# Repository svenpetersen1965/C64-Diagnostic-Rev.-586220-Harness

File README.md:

# C64-Diagnostic-Rev.-586220-Harness
The Diagnostic Rev. 586220 is a widely accepted test tool for the Commodore C64. It tests the RAM, ROMs and 
the peripheral chips (VIC, SID, CIA). To test all interfaces, a feedback is required. This is provided by this harness.

Find more information about the cable making involved <a href="http://tech.guitarsite.de/cable_making.html">on my website</a>

# Rev. 0

This repository contains all eagle files, gerber files, BOM, descriptions and cable drawings. The main documentation is contained in the User Port section.

Depending on where the parts and pcbs are purchased, the price for the complete harness is less than 20€ (2019).

Now, a 3D printed case for the user port and the cassette donge is designed and the stl files etc. are available here. 

# Rev. 1
Revision 1 is released now. It fixes the "False OK" of the Control Port test, while the keyboard dongle is inserted. This is a phenomenon, that applies to all sorts of harnesses for Diagnostic Rev. 586220. Please refer to <a src="http://tech.guitarsite.de/c64_diag_harness.html">my website</a>

# Extended Keyboard Dongle (do not build, unless you are sure, what it is required for)
A fix for existing harnesses is the <b>extended</b> Keyboard Dongle. It can be combined with Rev. 0 of this harness and all other Harnesses. It only requires a connection to the Cassette Port Dongle. It is not required with Rev. 1 of the harness or later. 

# Keyboard dongle with 90° header
Some people want to test the C64 mainboard while being mounted. The keyboard cable connector is conflicting here. Some leave out the strain relief. This is not a great solution. A 90° boc pin header can be used insted of the vertical one. This swapps the pins, due to a different orientation. Since the symmetrical pinning of the header and the non-directional properties of the analog switches, this does not matter and is working fine. I only build this kind of KB dongle now.

# The SMD Version
This version has no functional updates compared to Rev. 2 of the UP PCB and Rev. 1 of the Cassette SMD. Some prefer building SMD assemblies (me included). It is now fully tested.

# Recommended Screws
* For the case, I have used 2.9mm x 9.5mm (self taping) screws for sheet metal (C 2,9x9,5H, DIN 7981).  
* For mounting the optional slide switch: DIN 7985, M2x6
* For mounting the optional voltmeter: 2.2mm x 4.5mm (self taping) screws for sheet metal (C 2,2x4,5H, DIN 7981). 

# C128 diagnostics
They keyboard PCB for the C128 is released now and included in this repository. 

A cartridge with the Diagnostic Rev. 785260 software is required. I recommend using the <a href="https://github.com/bwack/Versa64Cart">Versa64cart</a> for this purpose. Other 8k generic cartridges might also be working. /EXROM and /GAME have to be HIGH/open.

The <b>C128D and C128D-CR</b> require a longer cable (1m) between the user port PCB and the Cassette port dongle. Both work with the <b>C128D Diagnostic Rev. 785260</b>.  The keyboard ribbon cable should be 90cm for the C128D.

The cassette port ribbon cable requires to be 25cm long for the C128 and 70cm long for the C128D/DCR.

The <b>C128D-CR</b> does not provide +5V at the keyboard D-Sub jack. The keyboard dongle <b>does not work</b> here. A solution needs to be developed.  

I have noticed, that not all female D-Sub connectors provide a proper contact with the pin header on the C128 mainboard. Please keep this in mind. The recommended type is Amphenol/FCI DB25S064TLF (Digikey 609-1519-ND, more sources in the BOM v1.1 or later). 

You might want to check out the 3D printed dongle case from <a href="https://www.thingiverse.com/thing:4602956">retrorewind.ca</a>.

# SX-64 Diagnostics
Diagnosing an SX/64 requires disconnecting the internal disk drive. A cassette port dongle cannot be used, so the analog switches for testing the control ports need to be switched manually. This is an option with teh User Port PCB Rev. 2.

Also the Keyboard can be tested with the C128 KB dongle and a gender changer.

The Diagnostic Rev. 586220++ is capable of detecting the SX-64 Kernal and then skip testing the cassette port.

# Other
you might want to check Jeff Birt's <a href="https://github.com/Jeff-Birt/COREi64_Dual_Diag_Cart_Case/tree/master">case</a> for the harness, too.

Find additional info about the harness on my <a href="http://tech.guitarsite.de/c64_diag_harness.html">website</a>.

Jeff Birt provided the information of the cable lengths for C128 diagnostics. This is part of the documentation now. 

# User Port PCB Rev. 2
The user Port PCB Rev. 2 fits into the User Port Case Rev. 1. It adds an option for the SX-64: Since the SX-64 has no
Cassette Port, the Feedbacks for the CVontrol Port are not switched automatically by the software. Rev. 2 allows to
switch on the feedbacks manually. A User Port Case for thei option has been made. It incorporates a cut out for a slide
switch (standard 19mm hole pitch). This switch can be connected top JP1. For this option the cutpad has to be cut open. 

# User Port PCB Rev. 3

The User Port Rev. 3 Dongle (THT and SMD versions in this repository) is providing two LED for voltage intocations (+5V and 9VAC). Further, there are pin headers for measuring those voltages at the user port. The +5V pin header allows connecting a 4 digit "precision" panel meter. I have some trust issues with those panel meters, but they are a nice light show.  

Nov. 2024: There is a new version of the case (the STLs are ending on "_noVM_SX.stl"). This version allows to measure the voltages at the pin headers with your multimeter and configure the SX64 or C64 option via jumper. That jumper should be the type with a "handle". 

<b>The solder bridge JP1 near the pin header J6 (which has to be placed) needs to be open!</b>

Therefore, it has to be cut along the gap with a scalpel or exacto knife. It is best to check the success with an ohmmeter/multimeter.

The cable for measuring the voltage (+5VDC and 9VAC) at the pin pin headers consists of two AWG24 wires, preferable in different colors, on one end is a two way Dupont connector, on the other end 4mm lab connectors. Holding them together with cable ties is maybe not such a bad idea.

To prevent short circuit, you should plug the lab connectors in the multimeter first, there are some security multimeter connectors, too. 

# Analog Switch IC (User Port Dongle)
Originally, the analog switches are <b>4066</b>. The 74HC4066 was also tested and works perfectly.

# BOM Value
The BOM values are calculated in May 2020. The calculation is based on the item prices from reichelt.de. They might differ from distributor to distributor. The edge connector prices are based on ebay shoppings. The calculated prices do not include any shipping fees. 

* User Port PCB plus cables and IEC dongle: 13.38€
* Cassette Port Dongle: 4.99€
* Keyboard Dongle: 1.85€
* C128 Keyboard Dongle: 3.23€

The 3D printed cases and the labels are not included in the price calculation.

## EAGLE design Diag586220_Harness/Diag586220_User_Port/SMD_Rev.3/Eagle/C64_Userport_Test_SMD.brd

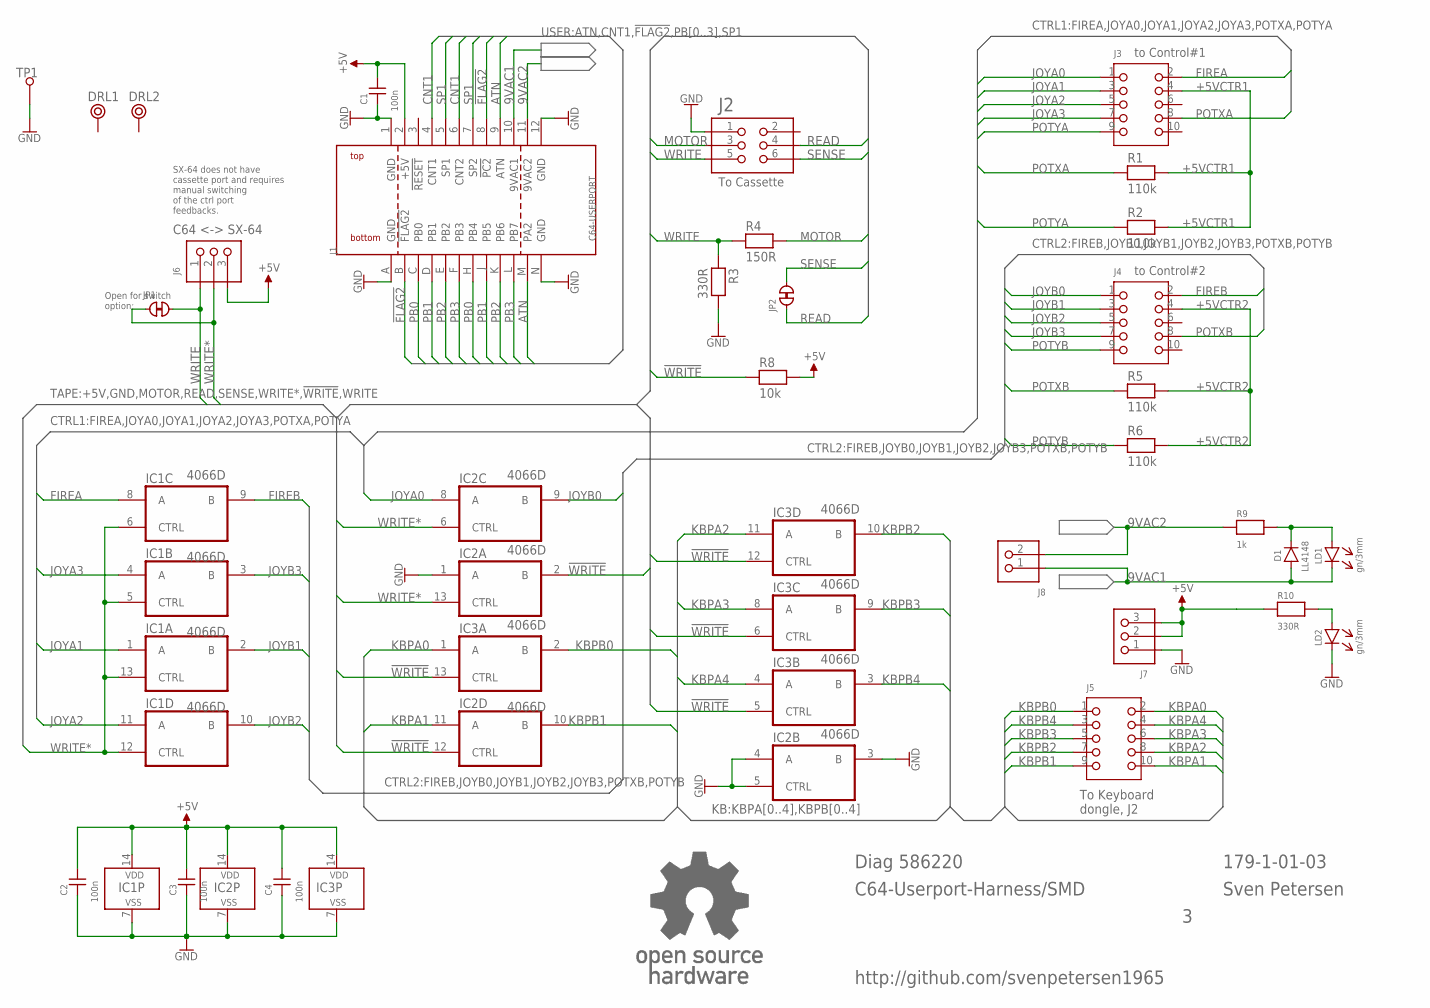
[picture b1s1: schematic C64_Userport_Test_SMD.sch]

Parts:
C1, C2, C3, C4: 100n; 0805
D1: LL4148; SOD80C
DRL1, DRL2: BOHR3,2
IC1, IC2, IC3: 4066D; SO14
J1: C64-USERPORT; USERPORT
J2: 2X03WV
J3, J4, J5: 2X05WV
J6, J7: PINHD-1X3; 1X03
J8: PINHD-1X2; 1X02
JP1, JP2: CLOSED; CP_CL
LD1, LD2: gn/3mm; 3MM
R1, R2, R5, R6: 110k; 0805
R3, R10: 330R; 0805
R4: 150R; 0805
R8: 10k; 0805
R9: 1k; 0805
TP1: L1,2_R; 1,2MM_R
U$20: OPEN_SOURCE_HW; OPENHW

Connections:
9VAC1: D1.A, J1.10 (9VAC1), J8.1, LD1.C (K)
9VAC2: J1.11 (9VAC2), J8.2, R9.1
!FLAG2: J1.8 (!PC2), J1.B (!FLAG2)
!WRITE: IC2.2 (B), IC2.12 (CTRL), IC3.5 (CTRL), IC3.6 (CTRL), IC3.12 (CTRL), IC3.13 (CTRL), R8.1
+5V: C1.2, C2.2, C3.2, C4.2, IC1.14 (VDD), IC2.14 (VDD), IC3.14 (VDD), J1.2 (+5V), J6.3, J7.2, J7.3, R8.2, R10.1
+5VCTR1: J3.4, R1.2, R2.2
+5VCTR2: J4.4, R5.2, R6.2
ATN: J1.9 (ATN), J1.M (PA2)
CNT1: J1.4 (CNT1), J1.6 (CNT2)
FIREA: IC1.8 (A), J3.2
FIREB: IC1.9 (B), J4.2
GND: C1.1, C2.1, C3.1, C4.1, IC1.7 (VSS), IC2.1 (A), IC2.3 (B), IC2.4 (A), IC2.5 (CTRL), IC2.7 (VSS), IC3.7 (VSS), J1.1 (GND), J1.12 (GND), J1.A (GND), J1.N (GND), J2.1, J7.1, LD2.C (K), R3.2, TP1.1
JOYA0: IC2.8 (A), J3.1
JOYA1: IC1.1 (A), J3.3
JOYA2: IC1.11 (A), J3.5
JOYA3: IC1.4 (A), J3.7
JOYB0: IC2.9 (B), J4.1
JOYB1: IC1.2 (B), J4.3
JOYB2: IC1.10 (B), J4.5
JOYB3: IC1.3 (B), J4.7
KBPA0: IC3.1 (A), J5.2
KBPA1: IC2.11 (A), J5.10
KBPA2: IC3.11 (A), J5.8
KBPA3: IC3.8 (A), J5.6
KBPA4: IC3.4 (A), J5.4
KBPB0: IC3.2 (B), J5.1
KBPB1: IC2.10 (B), J5.9
KBPB2: IC3.10 (B), J5.7
KBPB3: IC3.9 (B), J5.5
KBPB4: IC3.3 (B), J5.3
MOTOR: J2.3, R4.2
unnamed: D1.K, LD1.A, R9.2
unnamed: LD2.A, R10.2
PB0: J1.C (PB0), J1.H (PB4)
PB1: J1.D (PB1), J1.J (PB5)
PB2: J1.E (PB2), J1.K (PB6)
PB3: J1.F (PB3), J1.L (PB7)
POTXA: J3.8, R1.1
POTXB: J4.8, R5.1
POTYA: J3.9, R2.1
POTYB: J4.9, R6.1
READ: J2.4, JP2.1
SENSE: J2.6, JP2.2
SP1: J1.5 (SP1), J1.7 (SP2)
WRITE: J2.5, J6.1, JP1.2, R3.1, R4.1
WRITE*: IC1.5 (CTRL), IC1.6 (CTRL), IC1.12 (CTRL), IC1.13 (CTRL), IC2.6 (CTRL), IC2.13 (CTRL), J6.2, JP1.1

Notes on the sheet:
Diag 586220
C64-Userport-Harness/SMD
Sven Petersen
To Cassette
to Control#1
to Control#2
179-1-01-03
To Keyboard dongle, J2
C64 <-> SX-64
Open for switch option:
SX-64 does not have cassette port and requires manual switching of the ctrl port feedbacks.
http://github.com/svenpetersen1965

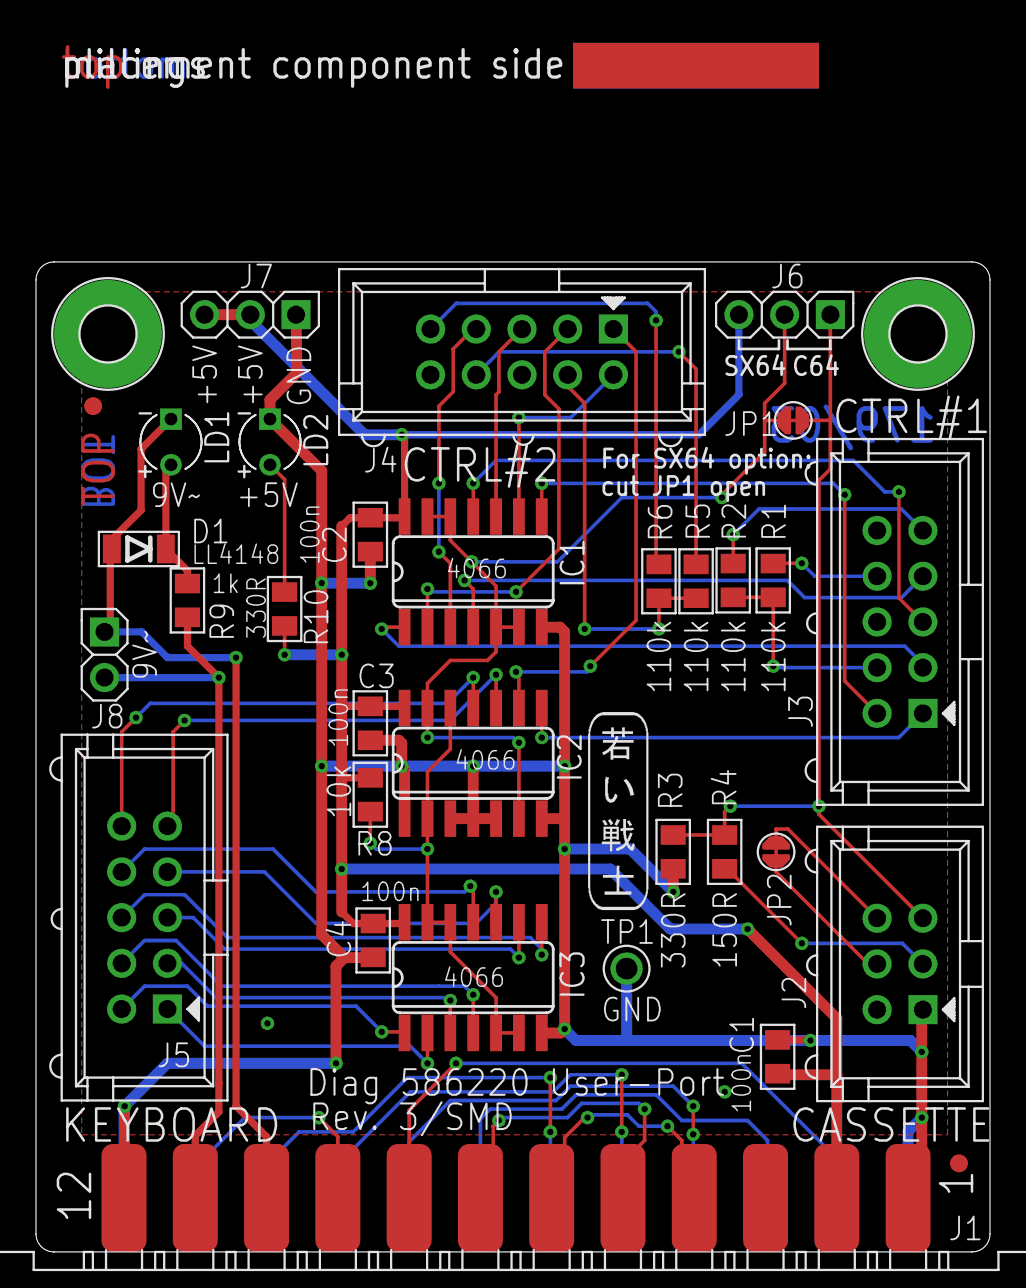
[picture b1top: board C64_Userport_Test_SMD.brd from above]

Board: 2 copper layers, 53.0 x 67.6 mm, 38 parts (1 on the bottom side), 46 nets.

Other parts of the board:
U$15: SVEN_TAG
U$17: 2LAYER
U$18: PCB-TITLE/
U$21, U$22: SMD_REF_R1MM

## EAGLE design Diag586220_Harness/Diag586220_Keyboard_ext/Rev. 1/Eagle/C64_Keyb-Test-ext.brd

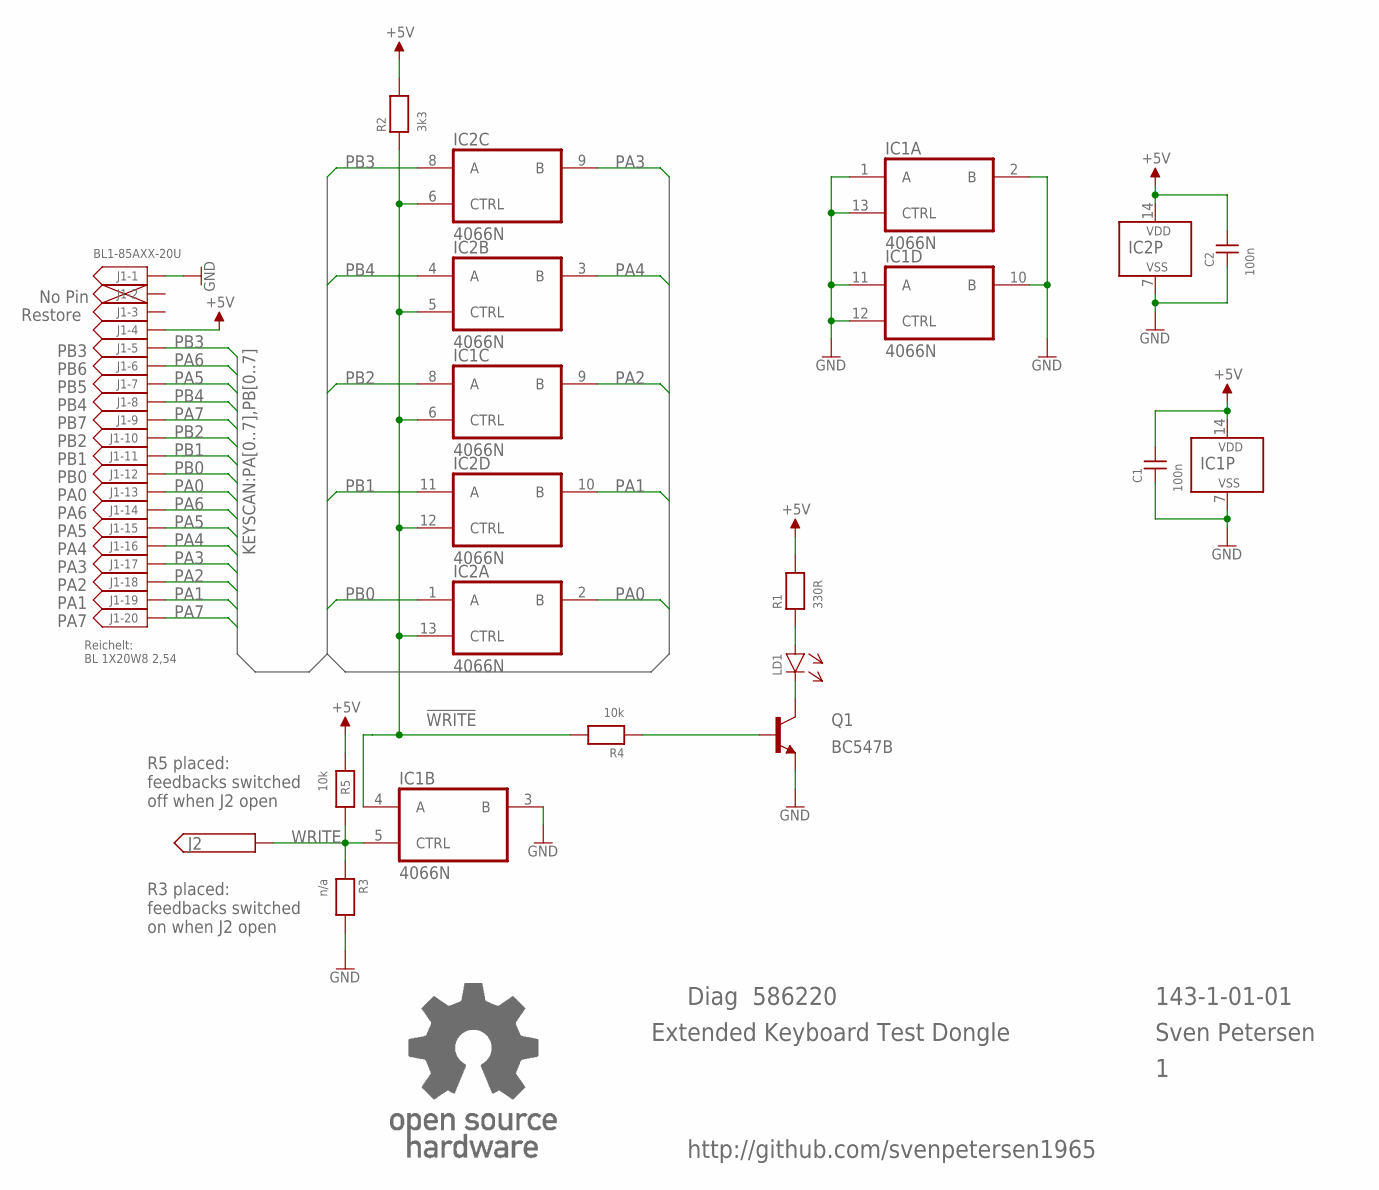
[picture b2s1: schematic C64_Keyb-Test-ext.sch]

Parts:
C1, C2: 100n; C-2,5
IC1, IC2: 4066N; DIL14
J1: BL1-85AXX-20U
J2: PINHD-1X1; 1X01
LD1: 3MM
Q1: BC547B; TO92
R1: 330R; R-10
R2: 3k3; R-10
R3: n/a; R-10
R4, R5: 10k; R-10
U$19: OPEN_SOURCE_HW; OPENHW

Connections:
!WRITE: IC1.4 (A), IC1.6 (CTRL), IC2.5 (CTRL), IC2.6 (CTRL), IC2.12 (CTRL), IC2.13 (CTRL), R2.1, R4.2
+5V: C1.2, C2.2, IC1.14 (VDD), IC2.14 (VDD), J1.4, R1.2, R2.2, R5.1
GND: C1.1, C2.1, IC1.1 (A), IC1.2 (B), IC1.3 (B), IC1.7 (VSS), IC1.10 (B), IC1.11 (A), IC1.12 (CTRL), IC1.13 (CTRL), IC2.7 (VSS), J1.1, Q1.1 (E), R3.2
unnamed: LD1.A, R1.1
unnamed: LD1.C (K), Q1.3 (C)
unnamed: Q1.2 (B), R4.1
PA0: IC2.2 (B), J1.13
PA1: IC2.10 (B), J1.19
PA2: IC1.9 (B), J1.18
PA3: IC2.9 (B), J1.17
PA4: IC2.3 (B), J1.16
PA5: J1.7, J1.15
PA6: J1.6, J1.14
PA7: J1.9, J1.20
PB0: IC2.1 (A), J1.12
PB1: IC2.11 (A), J1.11
PB2: IC1.8 (A), J1.10
PB3: IC2.8 (A), J1.5
PB4: IC2.4 (A), J1.8
WRITE: IC1.5 (CTRL), J2.1, R3.1, R5.2

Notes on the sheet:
PB3
PB6
PB5
PB4
PB7
PB2
PB1
PB0
PA0
PA6
PA5
PA4
PA3
PA2
PA1
PA7
No Pin
Restore
Diag 586220
Extended Keyboard Test Dongle
143-1-01-01
Sven Petersen
Reichelt: BL 1X20W8 2,54
R5 placed: feedbacks switched off when J2 open
R3 placed: feedbacks switched on when J2 open
http://github.com/svenpetersen1965

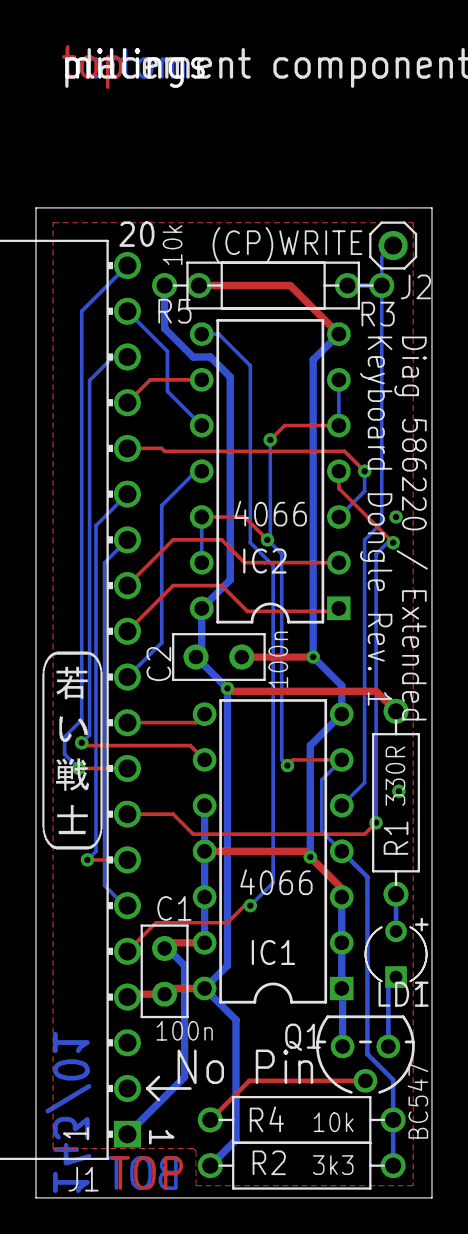
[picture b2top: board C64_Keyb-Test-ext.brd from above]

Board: 2 copper layers, 22.0 x 64.6 mm, 17 parts (1 on the bottom side), 20 nets.

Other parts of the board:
U$6: 2LAYER
U$7: PCB-TITLE/
U$17: SVEN_TAG

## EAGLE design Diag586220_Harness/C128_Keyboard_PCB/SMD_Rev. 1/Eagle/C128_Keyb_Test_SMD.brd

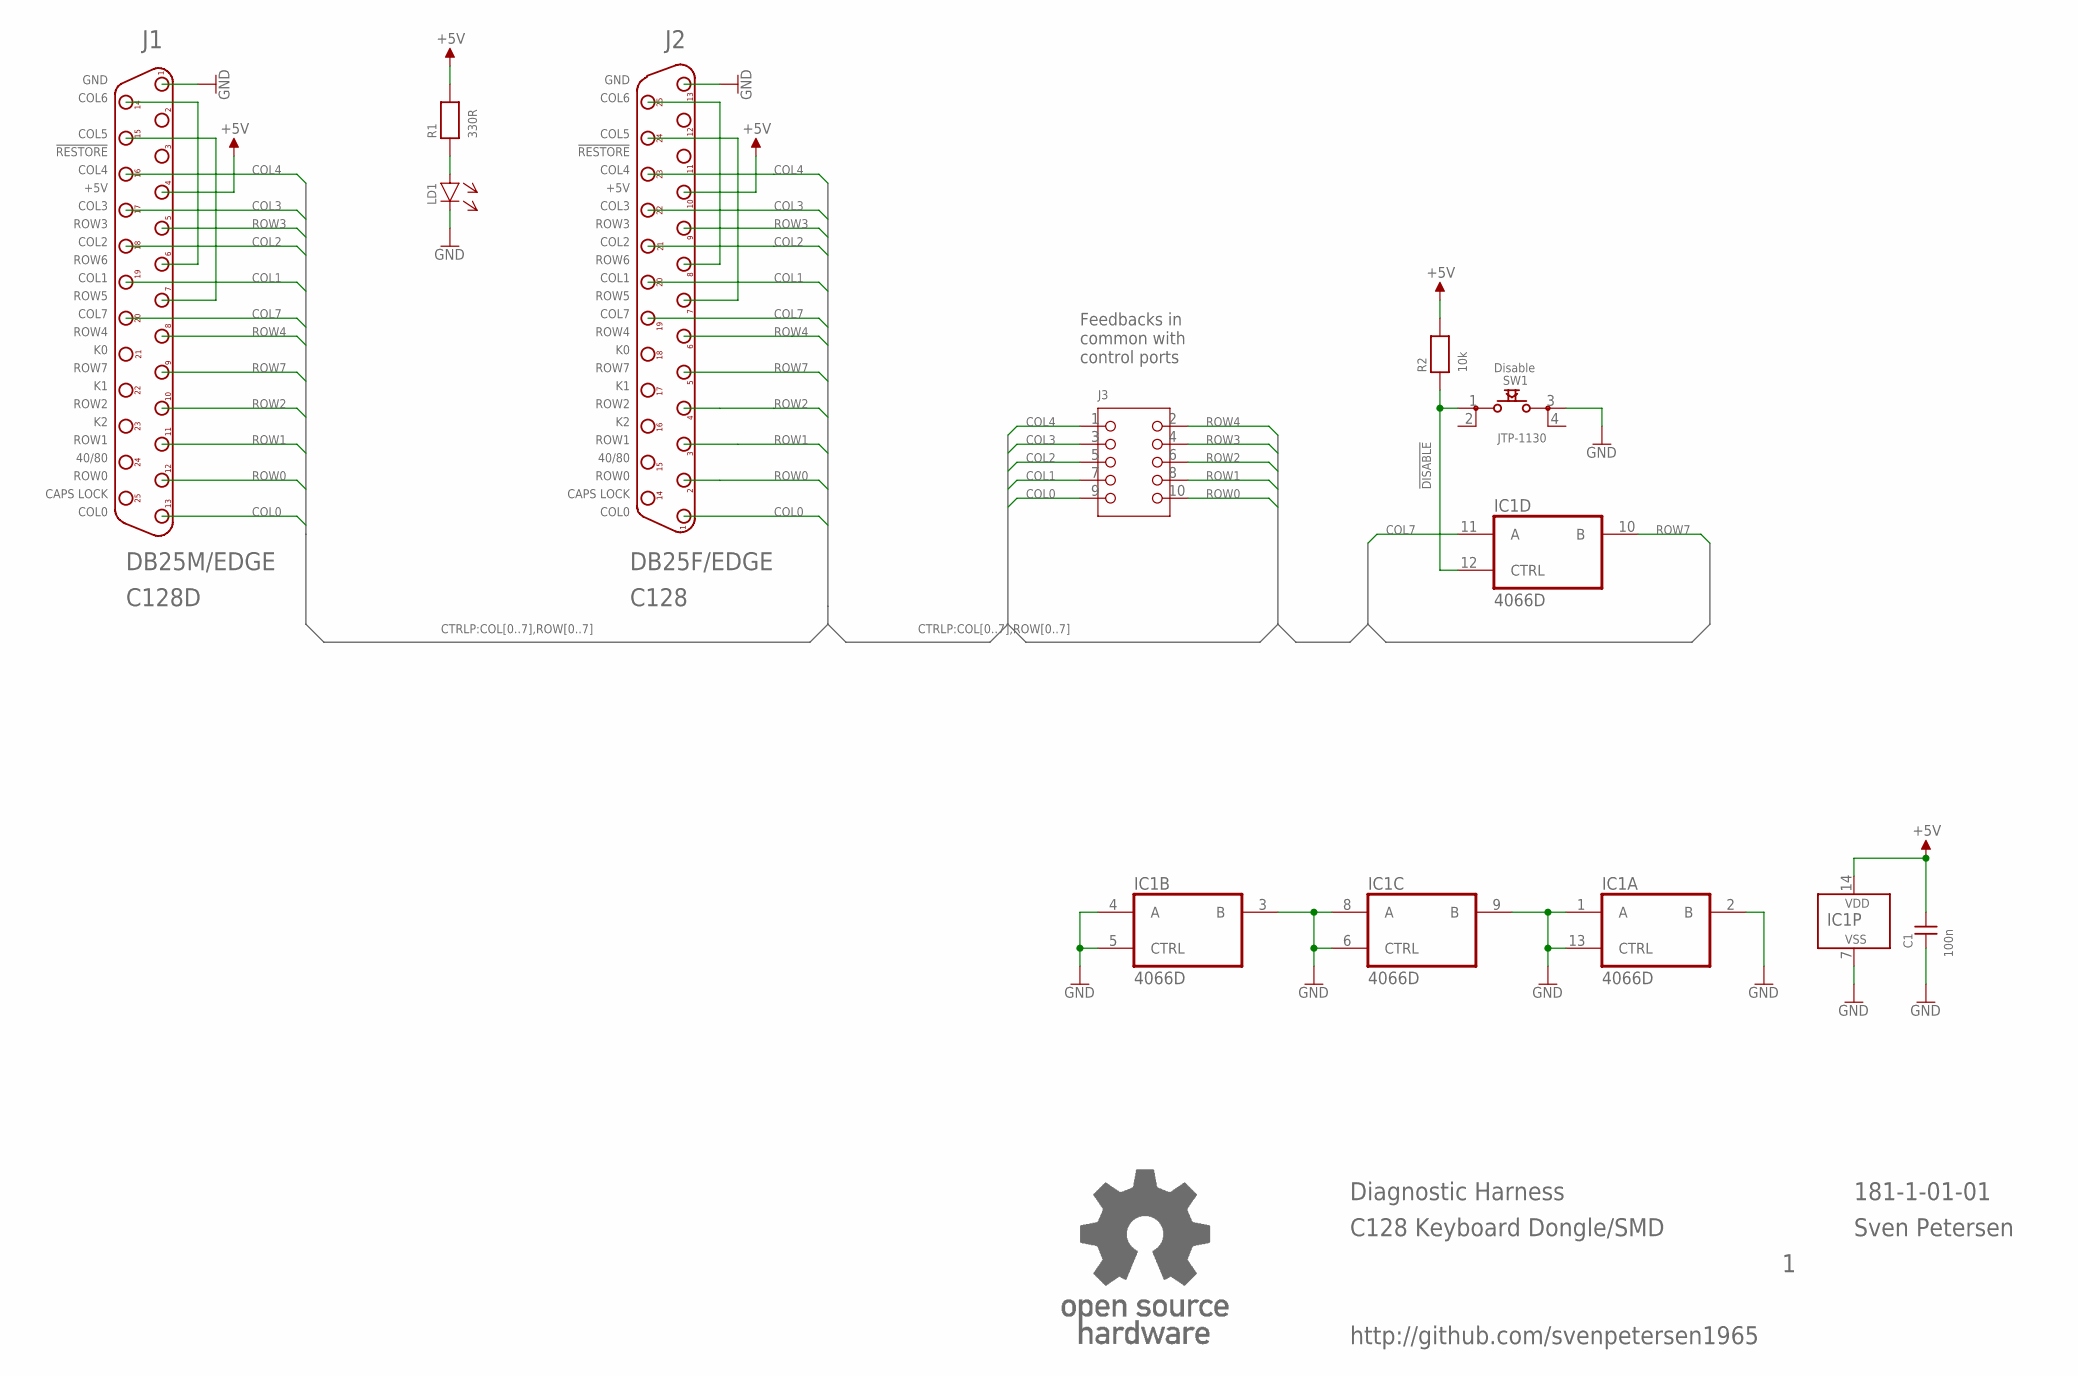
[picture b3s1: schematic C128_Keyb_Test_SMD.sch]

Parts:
C1: 100n; 0805
IC1: 4066D; SO14
J1: DB25M/EDGE; DB25M-EDGE
J2: DB25F/EDGE; DB25F-EDGE
J3: 2X05WV
LD1: 3MM
R1: 330R; 0805
R2: 10k; 0805
SW1: JTP-1130
U$20: OPEN_SOURCE_HW; OPENHW

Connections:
!DISABLE: IC1.12 (CTRL), R2.1, SW1.1
+5V: C1.2, IC1.14 (VDD), J1.4, J2.10, R1.2, R2.2
COL0: J1.13, J2.1, J3.9
COL1: J1.19, J2.20, J3.7
COL2: J1.18, J2.21, J3.5
COL3: J1.17, J2.22, J3.3
COL4: J1.16, J2.23, J3.1
COL7: IC1.11 (A), J1.20, J2.19
GND: C1.1, IC1.1 (A), IC1.2 (B), IC1.3 (B), IC1.4 (A), IC1.5 (CTRL), IC1.6 (CTRL), IC1.7 (VSS), IC1.8 (A), IC1.9 (B), IC1.13 (CTRL), J1.1, J2.13, LD1.C (K), SW1.3
unnamed: J1.6, J1.14
unnamed: J1.7, J1.15
unnamed: LD1.A, R1.1
unnamed: J2.7, J2.24
unnamed: J2.8, J2.25
ROW0: J1.12, J2.2, J3.10
ROW1: J1.11, J2.3, J3.8
ROW2: J1.10, J2.4, J3.6
ROW3: J1.5, J2.9, J3.4
ROW4: J1.8, J2.6, J3.2
ROW7: IC1.10 (B), J1.9, J2.5

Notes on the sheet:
Diagnostic Harness
C128 Keyboard Dongle/SMD
181-1-01-01
Sven Petersen
C128D
C128
ROW0
ROW1
ROW2
ROW3
ROW4
ROW5
ROW6
ROW7
COL0
COL1
COL2
COL3
COL4
COL5
COL6
COL7
!RESTORE
40/80
CAPS LOCK
GND
+5V
Feedbacks in common with control ports
Disable
http://github.com/svenpetersen1965

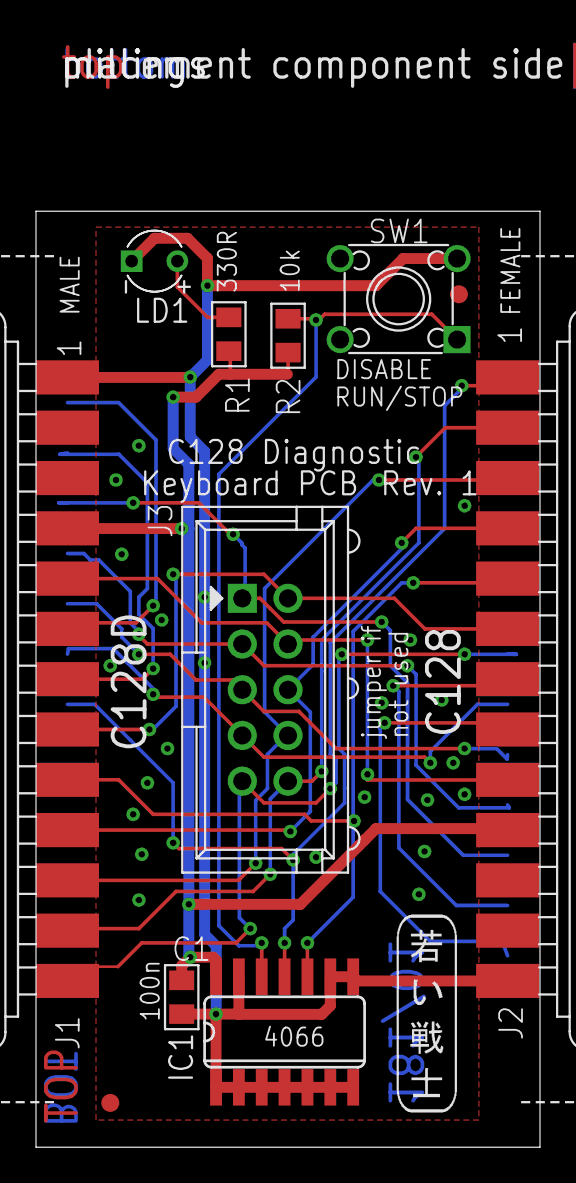
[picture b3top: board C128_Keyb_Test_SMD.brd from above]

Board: 2 copper layers, 28.0 x 61.7 mm, 15 parts (1 on the bottom side), 20 nets.

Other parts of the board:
U$8: 2LAYER
U$9: PCB-TITLE/
U$10: SVEN_TAG
U$21, U$22: SMD_REF_R1MM

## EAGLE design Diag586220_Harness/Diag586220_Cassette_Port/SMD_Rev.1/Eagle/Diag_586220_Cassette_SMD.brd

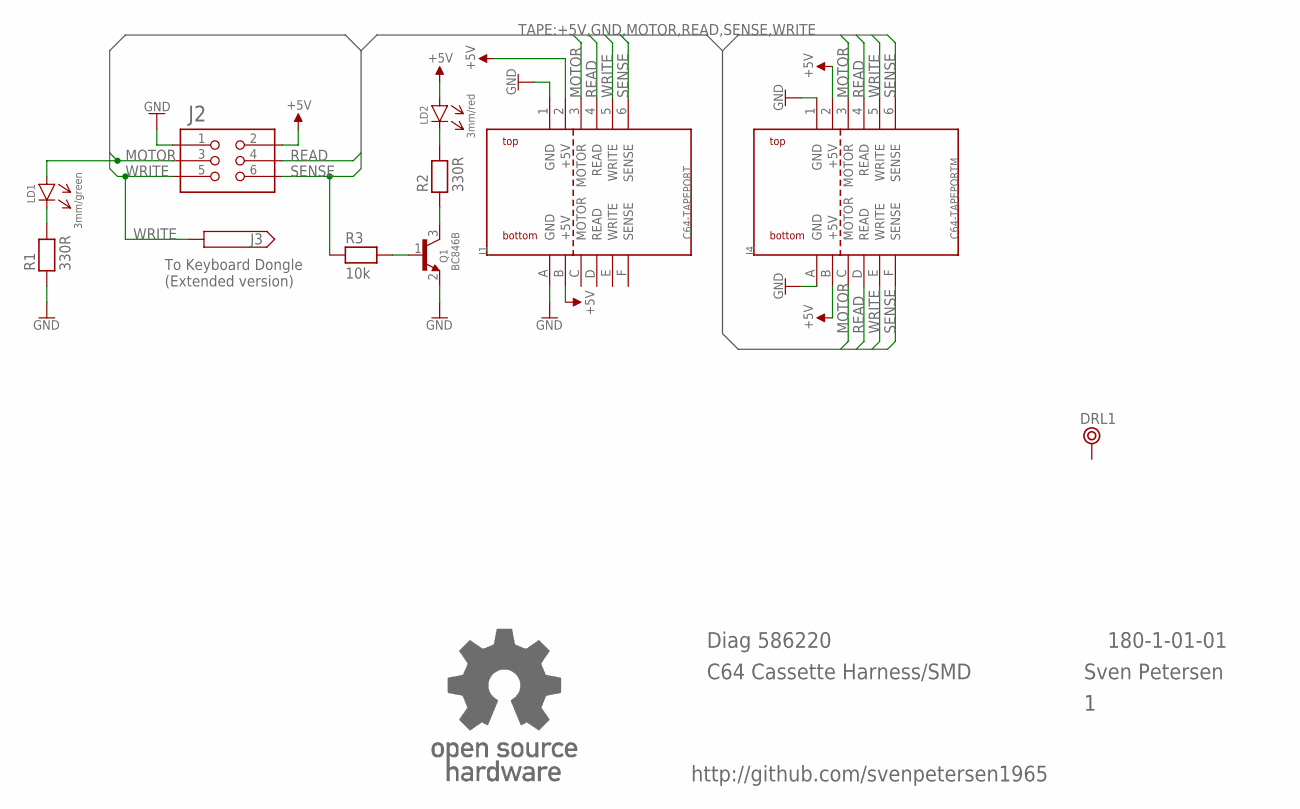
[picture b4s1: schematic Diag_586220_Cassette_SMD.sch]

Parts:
DRL1: BOHR3,5
J1: C64-TAPEPORT; TAPEPORT
J2: 2X03WV
J3: PINHD-1X1; 1X01
J4: C64-TAPEPORTM; TAPEPORT_M
LD1: 3mm/green; 3MM
LD2: 3mm/red; 3MM
Q1: BC846B; SOT23
R1, R2: 330R; 0805
R3: 10k; 0805
U$18: OPEN_SOURCE_HW; OPENHW

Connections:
+5V: J1.2 (+5V), J1.B (+5V), J2.2, J4.2 (+5V), J4.B (+5V), LD2.A
GND: J1.1 (GND), J1.A (GND), J2.1, J4.1 (GND), J4.A (GND), Q1.2 (E), R1.1
MOTOR: J1.3 (MOTOR), J2.3, J4.3 (MOTOR), J4.C (MOTOR), LD1.A
unnamed: LD1.C (K), R1.2
unnamed: Q1.1 (B), R3.2
unnamed: Q1.3 (C), R2.1
unnamed: LD2.C (K), R2.2
READ: J1.4 (READ), J2.4, J4.4 (READ), J4.D (READ)
SENSE: J1.6 (SENSE), J2.6, J4.6 (SENSE), J4.F (SENSE), R3.1
WRITE: J1.5 (WRITE), J2.5, J3.1, J4.5 (WRITE), J4.E (WRITE)

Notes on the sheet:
Diag 586220
C64 Cassette Harness/SMD
Sven Petersen
180-1-01-01
To Keyboard Dongle (Extended version)
http://github.com/svenpetersen1965

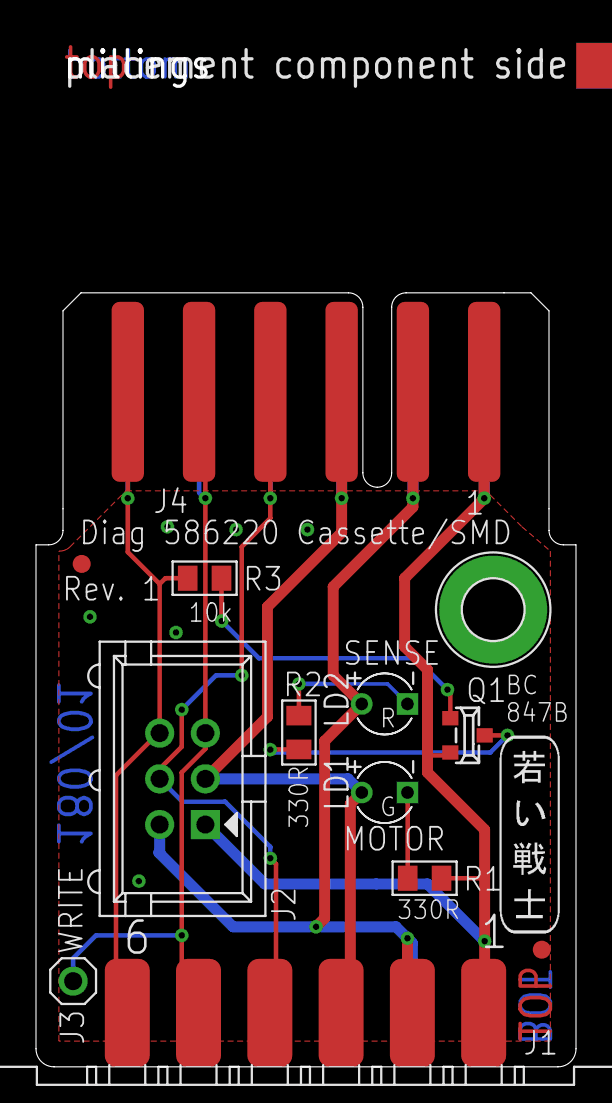
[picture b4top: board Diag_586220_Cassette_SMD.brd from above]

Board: 2 copper layers, 30.0 x 57.3 mm, 17 parts (1 on the bottom side), 10 nets.

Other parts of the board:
U$5: PCB-TITLE/
U$6: 2LAYER
U$11: SVEN_TAG
U$19, U$20: SMD_REF_R1MM

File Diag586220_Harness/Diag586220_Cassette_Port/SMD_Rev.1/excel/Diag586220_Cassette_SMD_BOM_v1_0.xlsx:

Diagnostic Rev. 586220 Harness - Cassette Port SMD Rev. 1
Bill of Material Rev. 1.0
Pos. | Qty | Value | Footprint | Ref.-No. | Comment
1 | 1 | 180-2-01-01 | 2 Layer | PCB Rev. 1 | 2 layer, Cu 35µ, HASL, 30.0mm x 43.0mm, 1.6mm FR4
2 | 1 | 2x6, 3.96mm pitch | C64-TAPEPORT | J1 | edge connector, C64 cassette port
3 | 1 | 2x3 box connector | 2X03WV | J2 | e.g. Reichelt WSL 6G
4 | 1 | 3mm/green | 3MM | LD1 | LED, 3mm, green
5 | 2 | 330R | 0805 | R1, R2 | 1/4 Watt, 5%
6 | 1 | BC846B | SOT23 | Q1 | Transistor, universal NPN (or BC847 etc.)
7 | 1 | 10K | 0805 | R3 | 1/4 Watt, 5%
8 | 1 | 3mm/red | 3MM | LD2 | LED, 3mm, red
9 | 1 | pin header 1p | 1x01 | J3 | Pin header for DuPont contact/do not place
10 | 1 | C64 Tapeport M | C64-TAPEPORTM | J4 | do not place. Structure in copper/PCB

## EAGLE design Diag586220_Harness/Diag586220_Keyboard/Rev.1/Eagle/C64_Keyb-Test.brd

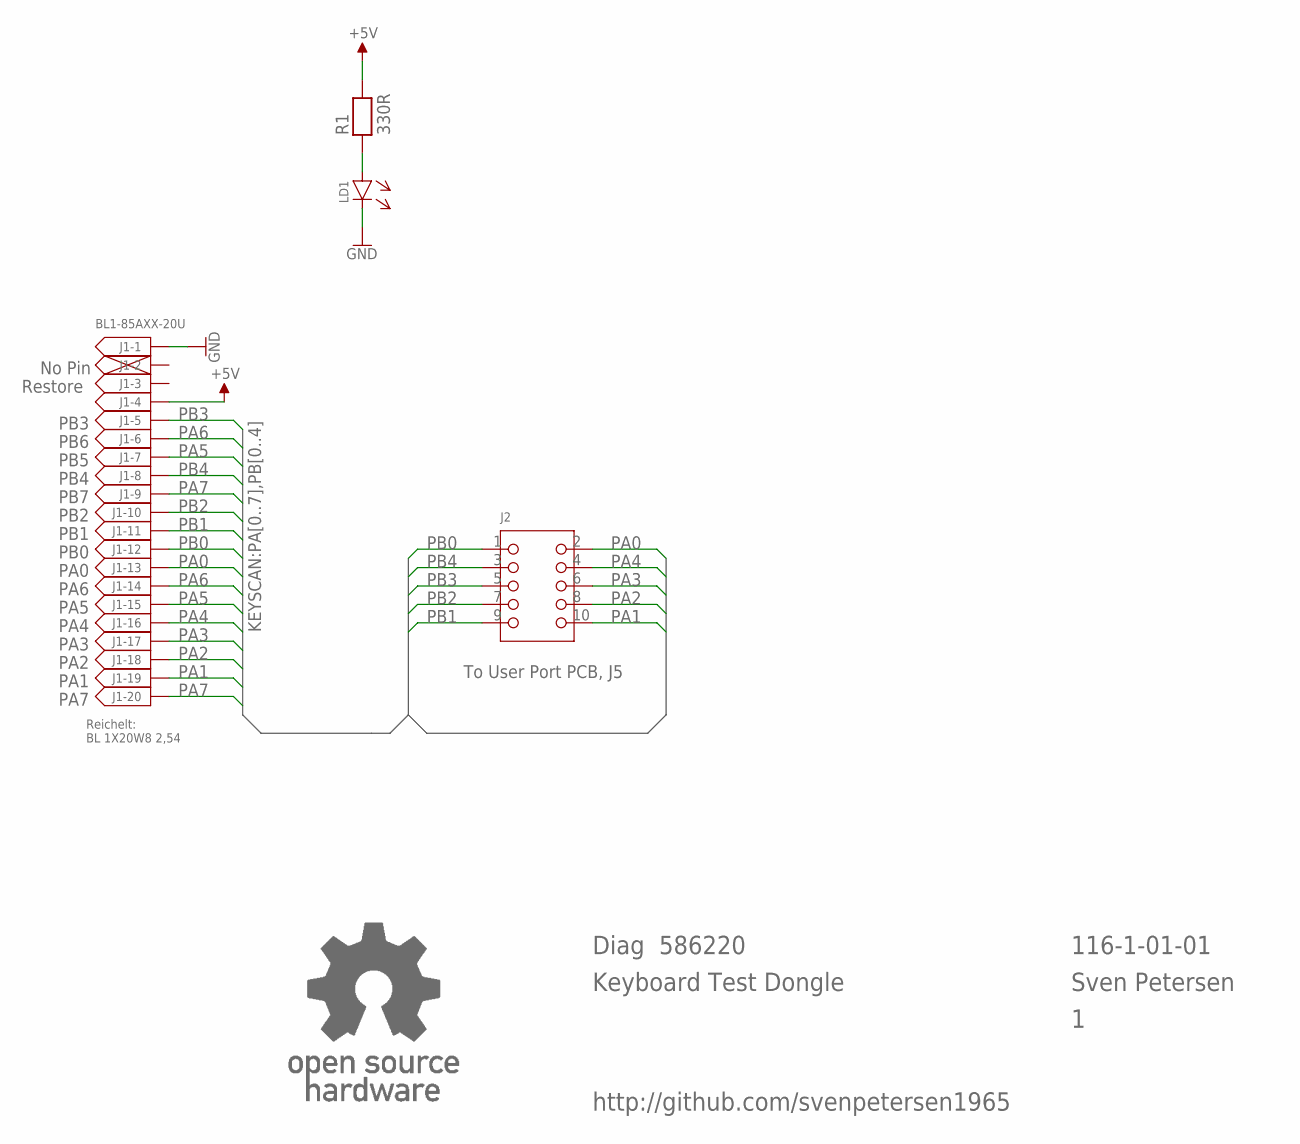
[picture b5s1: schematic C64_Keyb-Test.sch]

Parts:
J1: BL1-85AXX-20U
J2: 2X05WV
LD1: 3MM
R1: 330R; R-10
U$9: OPEN_SOURCE_HW; OPENHW

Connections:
+5V: J1.4, R1.2
GND: J1.1, LD1.C (K)
unnamed: LD1.A, R1.1
PA0: J1.13, J2.2
PA1: J1.19, J2.10
PA2: J1.18, J2.8
PA3: J1.17, J2.6
PA4: J1.16, J2.4
PA5: J1.7, J1.15
PA6: J1.6, J1.14
PA7: J1.9, J1.20
PB0: J1.12, J2.1
PB1: J1.11, J2.9
PB2: J1.10, J2.7
PB3: J1.5, J2.5
PB4: J1.8, J2.3

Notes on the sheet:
PB3
PB6
PB5
PB4
PB7
PB2
PB1
PB0
PA0
PA6
PA5
PA4
PA3
PA2
PA1
PA7
No Pin
Restore
Diag 586220
Keyboard Test Dongle
116-1-01-01
Sven Petersen
Reichelt: BL 1X20W8 2,54
To User Port PCB, J5
http://github.com/svenpetersen1965

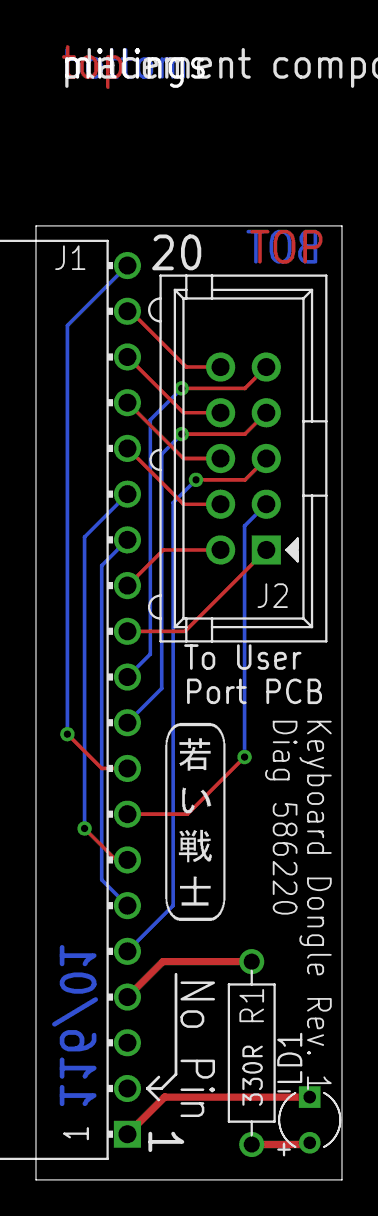
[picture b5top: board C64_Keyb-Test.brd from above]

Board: 2 copper layers, 17.0 x 63.6 mm, 8 parts (1 on the bottom side), 16 nets.

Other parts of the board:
U$6: 2LAYER
U$7: PCB-TITLE/
U$8: SVEN_TAG

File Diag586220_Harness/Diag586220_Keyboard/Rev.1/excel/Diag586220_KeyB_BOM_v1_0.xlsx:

Diagnostic Rev. 586220 Harness - Keyboard Dongle Rev. 1
Bill of Material Rev. 1.0
Pos. | Qty | Value | Footprint | Ref.-No. | Comment
1 | 1 | 116-2-01-00 | 2 Layer | PCB Rev. 1 | 2 layer, Cu 35µ, HASL, 53.0mm x 17.0mm, 1.6mm FR4
2 | 1 | BL1-85AXX-20U | BL1-85AXX-20U | J1 | e.g. MPE Garry, Reichelt BL 1x20W8 2,54
3 | 1 | 3mm/green | 3MM | LD1 | LED
4 | 1 | 330R | R-10 | R1 | 1/4 Watt, 5%
5 | 1 | boxed pin header 2x5, 2.54mm pitc | 2x05WV | J2 | e.g. Reichelt WSL 10G

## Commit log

2019-03-14 Initial upload of Rev. 0
    Initial upload of Rev. 0
2019-03-14 Added picture
    Picture of the diagnostic 586220+ Rev. 0.4 in operation
2019-03-14 Readme created
    repository description
2019-03-25 Typos removed
2019-04-08 Corrected the wrong file names
    Both file names were confused.
2019-04-13 BOM v0.0 is obsolete
    BOM v0.1 is valid. Only a comment about a resistor is inserted, material is the same like v0.0
2019-04-13 Added a comment about the 320R resistor R3
2019-05-29 Create LICENSE
2019-11-07 Added the BOM created by ChrisToast89
    for Digikey N.America. This BOM was noch checked.
2020-02-14 Add files via upload
    values from 120k to 110k and 320R to 316R
2020-02-14 Add files via upload
    BOM v0.2
2020-02-14 BOM v0.2
2020-03-11 Add files via upload
    Rev. 1 released
2020-03-11 Rev. 1 released
2020-03-11 New release
2020-03-11 BOM v1.0
2020-03-11 old BOM not required
2020-03-11 New cases for Rev. 1 boards
2020-03-11 Fixed the LD1 naming of LD2 in BOM
2020-03-11 Fixed LD2 in BOM
2020-03-15 Slightly new top shell allows higher sockets
2020-03-15 Slightly modified top shell allows higher sockets
2020-03-15 re-arranged directories
2020-03-15 Slightly modified drawing
    The 10th wire of the ribbon cable is clearly shown as clipped now.
2020-03-15 slightly improved cable drawing
2020-04-25 Added Information for C128 diagnostics
    The user port - cassette port cable and the user port - keyboard PCB cable need to be longer for C128. This information is now included.
2020-04-25 Added cable lengthinfo for C128 diagnostics
    The user port to cassette port dongle cable needs to be longer for 128 diagnostics. The same is required for the user port to keyboard dongle cable.
2020-05-03 Added a price calculation (estimation)
    The prices depend on the sources, you buy the parts from, so it is an estimation. It includes the cables, but not the 3D printed cases.
2020-05-16 C128 Keyboard PCB released
2020-05-26 Added the price calculation for C128 Keyboard PCB
2020-06-10 Gerbers Rev. 1a replace Rev. 1
    The silk screen was changed (C4)
2020-06-10 Silk screen modified (C4)
2020-06-10 Silk Screen changed (C4)
2020-06-10 Silk Screen modified
    Gerbers v1a replace v1
2020-06-10 Silk Screen modified
2020-06-10 Scilk Screen modified
2020-08-10 Rev. 2 released
    Revision 2 adds a switch option for SX-64. Default is still C64.
2020-08-10 Case for the SX-64 Switch option released
    This fits the User Port Case Rev. 1 and Rev. 2.
2020-08-11 Silk Screen Update
2021-04-19 SMD version of UP Rev. 2
    SMD Version for easier assembly, untested
2021-04-19 SMD Version of CP Rev. 1
    SMD version for easier assembly
2021-04-19 SMD version
2021-07-14 BOM update
2021-07-20 SMD version tested "ok"
2021-07-20 SMD version photographed
2021-07-20 KB Dongle with 90° pin header
2021-12-25 Improved cases
    Rev. 1.1 is a slightly improved case for Rev. 1 boards and later
2021-12-26 Oshpark compatible Gerber added
2021-12-26 Oshpark compatible gerbers added
2022-01-03 Explained the Amphenol DB25S064TLF
    and added more sources and order numbers.
2022-01-03 Pictures added
2022-01-17 BOM Rev. 1.1
    R2 and R4 values have changed
2022-01-17 BOM v1.1
    R2 and R4 values are changed
2022-01-17 Gerber V1c released
    Changed the value for R2 and R4
2022-01-17 BOM v1.1 updated
    The values for R2 and R4 have been changed
2022-02-26 Gerbers removed
2022-08-29 Case for Userport PCB Rev. 3
    There are two versions of this case:
    With voltmeter and without voltmeter.
2022-08-29 Case for Userport PCB Rev. 3
2022-12-17 Presentation of Dec. 17th, 2022
2023-02-05 Delete Diag586220_Harness/Case (3D print) directory
    Reorganizing the directory structure
2024-05-25 User Port Rev. 3 released
2024-05-25 UP SMD Rev. 3
    User Port SMD Rev. 3 released
2024-05-29 Recommended Screws updated
2024-07-18 Corrected Silkscreen (Value R3)
    R3 was still 316R and has to be 330R on the silk screen
2024-07-18 Fixed BOM
    The BOM v3.0 in pdf was obsolete before publishing, I have replaced the value of R3. It was correct in Eagle and the rest of the documentation.
2024-09-09 Update README.md
    74HC4066
2024-11-06 New verson with SX-64 option
    Now, it is possible to print a case that provides access to the pin header and jumper for SX64/C64 configuration
2024-11-06 New case with SX-64 option jumper
    Now, it is possible to print a case that provides access to the pin header and jumper for SX64/C64 configuration .
2024-11-06 Add files via upload
    Now, it is possible to print a case that provides access to the pin header and jumper for SX64/C64 configuration.
2024-11-06 case w SX64-C64 jumper access
    Pictures added
2024-11-06 Cable for voltage measurement
2024-11-06 Introduced the new case with SX64-C64 jumper
2025-11-27 Documentation improved
